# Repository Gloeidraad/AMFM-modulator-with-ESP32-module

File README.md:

This is an MP3 player, Web-radio player, Bluetooth player, and simple waveform generator, based on an ESP32 module. 
The output is connected to a simple FM/AM modulator. The player is intended for collectors and enthusiasts of old
(tube) radios.

The original design (V1.5) has been made with KiCad 7.0. The updated design (V1.7) has been made with KiCad 8.0.

I also added some of the specific 3D models.

Note: In many countries it is not allowed to build radio transmitters. Although this design has a range of only a 
few meters, building it is at your own risk.

Additional information can be found at: 

https://www.transistorforum.nl/forum/index.php?id=77783 and https://www.transistorforum.nl/forum/index.php?id=82213

It is in Dutch, so please use some translate program...

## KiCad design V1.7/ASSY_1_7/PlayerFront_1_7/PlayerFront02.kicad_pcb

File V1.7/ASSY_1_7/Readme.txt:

This section contains designs for a front and back panel for the AM/FM modulator. You find them in the PlayerBack_1_7 and PlayerFront_1_7 directories. You can order the panels at a PCB supplyer or any other panel manufacturer. I recommend a panel thickness of 1 or 1.2 mm. Note that the front panel has also some electronics desing at the back side. This is not used the for player, and can be left wihtout electronic parts.

The main desing (PLL_AM_OSC_1_7_ASSY) is not intended for fabrication, but serves only as a model to show the complete design (case, PCBA, and panels).

Please unzip PLL_AM_OSC_1_7.zip in folder 3D before opening PLL_AM_OSC_1_7_ASSY.kicad_pro

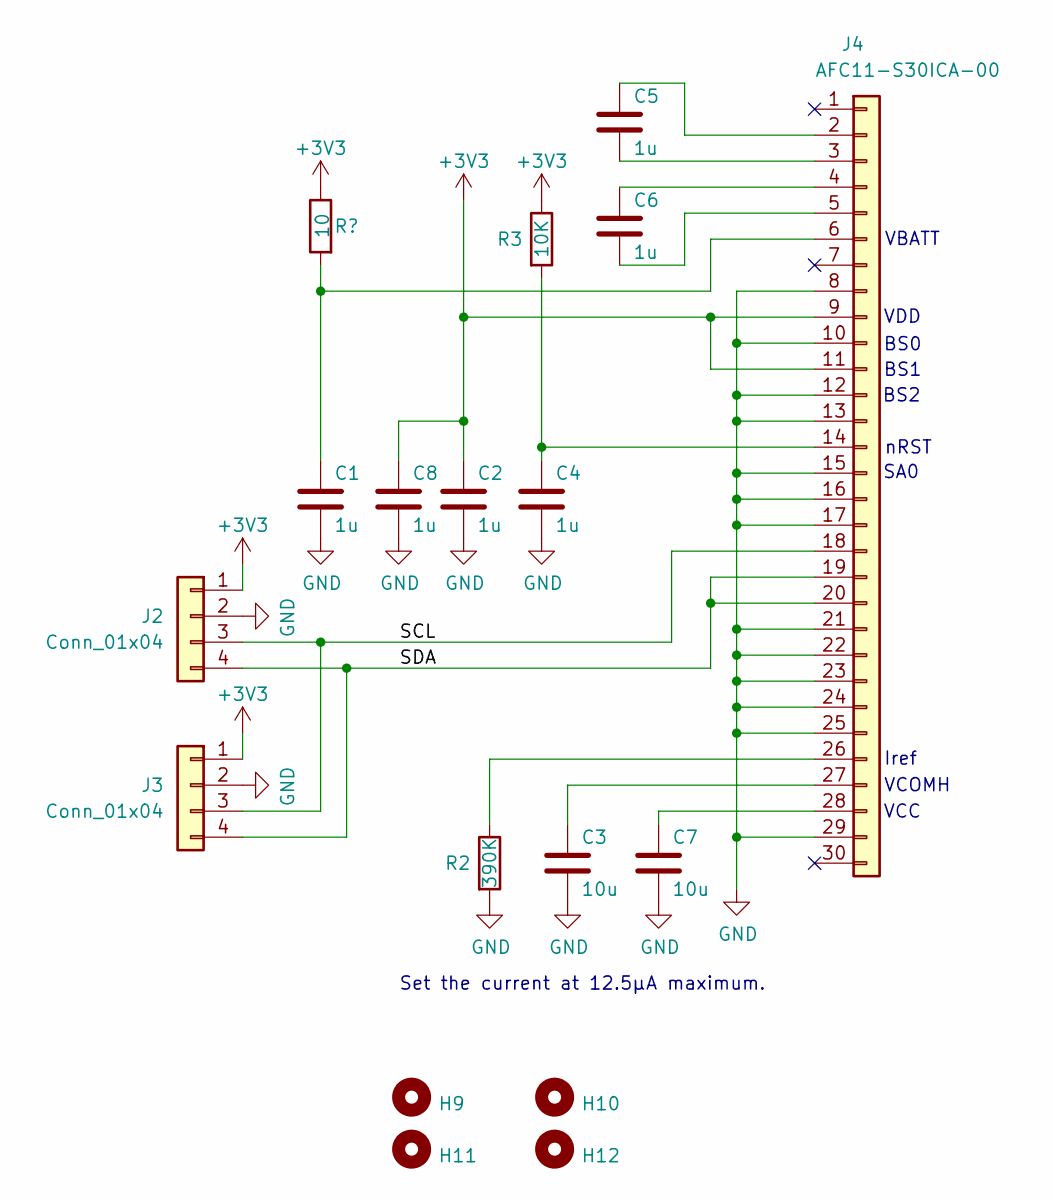
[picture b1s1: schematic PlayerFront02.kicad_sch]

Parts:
C1, C2, C4, C5, C6, C8: 1u; C_1206_3216Metric_Pad1.33x1.80mm_HandSolder
C3, C7: 10u; C_1206_3216Metric_Pad1.33x1.80mm_HandSolder
H9, H10, H11, H12: MountingHole; MountingHole_3.5mm
J2: Conn_01x04; HeaderMale_1x04_P2.54mm_Vertical_SMD
J3: Conn_01x04; PinHeader_1x04_P2.54mm_Vertical_SMD_Pin1Left
J4: AFC11-S30ICA-00; AFC11-S30ICA-00 FFC FPC Connector 0.5mm Pitch 30 pins VERTI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
R2: 390K; R_1206_3216Metric_Pad1.30x1.75mm_HandSolder; JLC C23150
R3: 10K; R_1206_3216Metric_Pad1.30x1.75mm_HandSolder
R10: 10; R_1206_3216Metric_Pad1.30x1.75mm_HandSolder

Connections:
+3V3: C2.1, C8.1, J2.1, J3.1, J4.9, J4.11, R3.1; also elsewhere on the board
/SCL: J2.3, J3.3, J4.18
/SDA: J2.4, J3.4, J4.19, J4.20
GND: C1.2, C2.2, C3.2, C4.2, C7.2, C8.2, J2.2, J3.2, J4.8, J4.10, J4.12, J4.13, J4.15, J4.16, J4.17, J4.21, J4.22, J4.23, J4.24, J4.25, J4.29, R2.2
unnamed: C5.1, J4.2
unnamed: C5.2, J4.3
unnamed: C6.1, J4.4
unnamed: C6.2, J4.5
unnamed 8: C1.1, J4.6; also elsewhere on the board
unnamed: C4.1, J4.14, R3.2
unnamed: J4.26, R2.1
unnamed: C3.1, J4.27
unnamed: C7.1, J4.28

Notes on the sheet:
Set the current at 12.5μA maximum.
VDD
SA0
BS2
BS0
nRST
Iref
VCOMH
VBATT
VCC
BS1

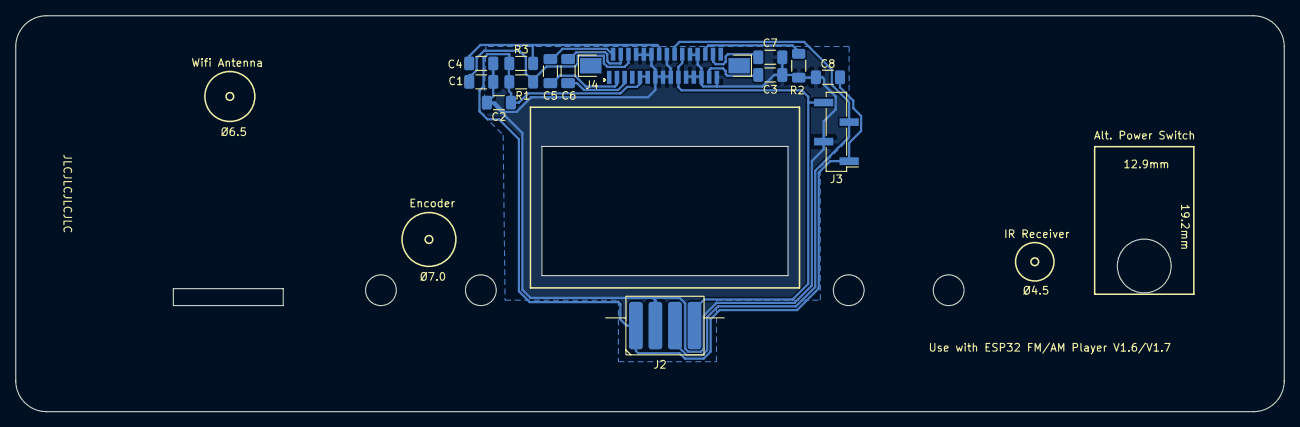
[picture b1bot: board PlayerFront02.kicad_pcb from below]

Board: 2 copper layers, 165.0 x 51.5 mm, 18 parts (14 on the bottom side), 13 nets.

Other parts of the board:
R1: 10; R_1206_3216Metric_Pad1.30x1.75mm_HandSolder

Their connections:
+3V3: R1.1; also elsewhere on the board
unnamed 8: R1.2; also elsewhere on the board

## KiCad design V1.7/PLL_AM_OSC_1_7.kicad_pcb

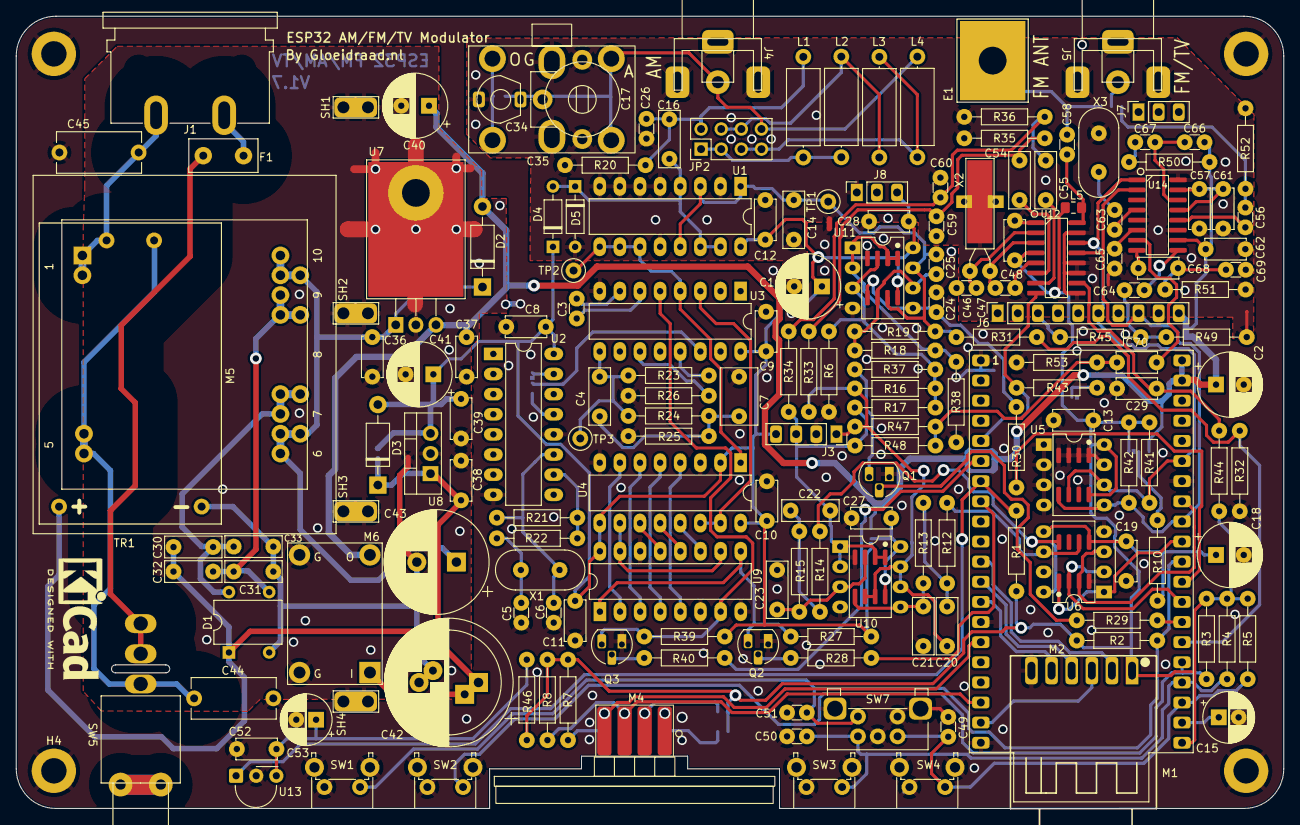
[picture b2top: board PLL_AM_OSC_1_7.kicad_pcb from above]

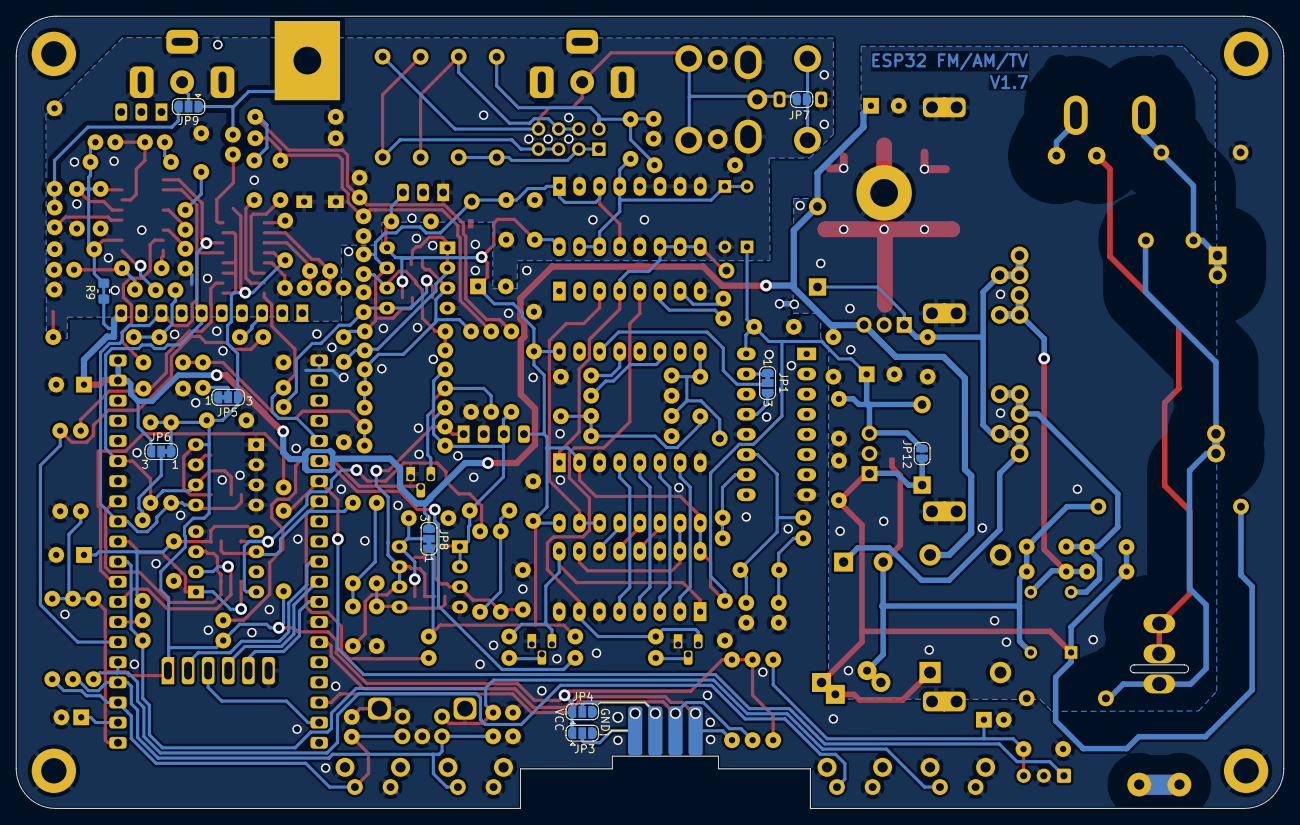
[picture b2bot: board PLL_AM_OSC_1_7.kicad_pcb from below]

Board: 2 copper layers, 160.0 x 100.0 mm, 198 parts (11 on the bottom side), 117 nets.

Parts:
C1, C40, C41: 220µF; CE_Radial_D8.0mm_P3.50mm_E2.0mm
C2: 1000µF; CE_Radial_D8.0mm_P3.50mm_E2.0mm
C3: 100p; C_CER_D30_W16_P25_E20_H08
C4, C54, C55: 100n; C_MKT_L70_W25_P50__E20_H08
C5, C25: 47p; C_CER_D30_W16_P25_E20_H08
C6, C63: 27p; C_CER_D30_W16_P25_E20_H08
C7: 470n; C_MKT_L70_W45_P50__E20_H08
C8, C9, C10, C11, C12, C13, C19, C27, C28, C29, C36, C37, C38, C39, C48, C52, C57, C61: 100n; C_CER_D50_W25_P50_E20_H08
C14: 2n2; C_MKT_L70_W25_P50__E20_H08
C15: 10µF; CE_Radial_D6.3mm_P2.50mm_E2.0mm
C16: 10n; C_MKT_L70_W25_P50__E20_H08
C17: 120p; GZC18100
C18: 100µF; CE_Radial_D8.0mm_P3.50mm_E2.0mm
C20, C22: 1n; C_MKT_L70_W25_P50__E20_H08
C21, C23: 470p; C_MKT_L70_W25_P50__E20_H08
C24, C49, C50, C51, C56, C64: 10n; C_CER_D30_W16_P25_E20_H08
C26, C46, C47: 15p; C_CER_D30_W16_P25_E20_H08
C30, C31, C32, C33: 22n; C_MKT_L70_W25_P50__E20_H08
C34: 120p; TZ03
C35: 142+59 pF; CAP-VAR-223P-NO-CY
C42: 1000µF; CE_Radial_D16.0mm_P7.50_P5.00mm_E2.4mm
C43: 2200µF; CP_Radial_D13.0mm_P5.00mm
C44, C45: 4n7/Y1; C_Disc_D10.5mm_W5.0mm_P10.00mm
C53: 10u; CE_Radial_D6.3mm_P2.50mm_E2.0mm
C58: 4p7; C_CER_D30_W16_P25_E20_H08
C59, C60: 220p; C_CER_D30_W16_P25_E20_H08
C62: 1µF; C_CER_D50_W25_P50_E20_H08
C65: 470p; C_CER_D30_W16_P25_E20_H08
C66, C69: 22n; C_CER_D30_W16_P25_E20_H08
C67: 47n; C_CER_D30_W16_P25_E20_H08
C68, C70: 220n; C_CER_D50_W25_P50_E20_H08
D1: DIL4/1A; Diode_Bridge_DIP-4_W7.62mm_P5.08mm
D2, D3: 1N4001; D_DO-41_SOD81_P10.16mm_Horizontal
D4, D5: BAT85; D_DO-35_SOD27_P7.62mm_Horizontal
E1: ANTENNA; ANTENNA-V3MM5
F1: 100mA; Fuse_Littelfuse_392Series
H1, H2, H3, H4: MountingHole; MountingHole_3.2mm_M3_DIN965_Pad
J1: 230V~; EURO_AC_BX-180_Movable
J3: Conn_01x04; HeaderFemale_1x04_P2.54mm_Vertical
J4, J5: Keystone 900; Keystone RCA
J6: VIDEO-MODULE; HeaderFemale_1x10_P2.54mm_Vertical
J7, J8: Conn_01x03_Socket; HeaderFemale_1x03_P2.54mm_Vertical
JP1, JP5, JP6, JP8: SolderJumper_3_Bridged12; SolderJumper-3_P1.3mm_Bridged12_RoundedPad1.0x1.5mm_NumberL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
JP2: LSEL; PinHeader_2x04_P2.54mm_Vertical
JP3, JP4, JP9: SolderJumper_3_Bridged12; SolderJumper-3_P1.3mm_Open_RoundedPad1.0x1.5mm
JP7: SolderJumper_Mini_2_Open; SolderJumper-2_P1.3mm_Open_RoundedPad1.0x1.5mm
JP12: SolderJumper_2_Open; SolderJumper-2_P1.3mm_Open_RoundedPad1.0x1.5mm
L1, L2: 330 µH; L_Axial_L9.5mm_D4.0mm_P12.70mm_Horizontal
L3: 180 µH; L_Axial_L9.5mm_D4.0mm_P12.70mm_Horizontal
L4: 100 µH; L_Axial_L9.5mm_D4.0mm_P12.70mm_Horizontal
L5: 120nH; L_0805_2012Metric_Pad1.15x1.40mm_HandSolder
M1: ESP32-WROVER-CAM-40P; ESP32-WROVER-DEV_ON_HEADERS_BARE
M2: µSD CARD MODULE; MOD-USD-ADAPTER18X18-type2
M4: OLED-128x64; OLED128X64-1.3inch-P4-Card-Edge-dual
M5: Hi-Link HLK-5M15; HiLink_5Mxx
M6: CN3903 5V/3A Module; MOD-DC-DC-DUAL
MECH1: KiCad Logo; KiCad-Logo2_6mm_SilkScreen
NT1, NT2, NT3: NetTie_2; NetTie-2_SMD_Pad0.7mm
Q1, Q2, Q3: 2N7000; TO-92_HandSolder
R1, R2, R3, R4, R5, R7, R8, R27, R30, R39, R41, R42, R43, R44: 10k; R_Axial_L6.0mm_D2.0mm_P10.16mm_Horizontal
R6: 100k; R_Axial_L6.0mm_D2.0mm_P10.16mm_Horizontal
R9: 1R; R_0805_2012Metric_Pad1.20x1.40mm_HandSolder
R10, R46: 10R; R_Axial_L6.0mm_D2.0mm_P10.16mm_Horizontal
R12, R13, R14, R15, R35, R36: 7k5; R_Axial_L6.0mm_D2.0mm_P10.16mm_Horizontal
R16, R17, R18, R31, R38, R53: 30k; R_Axial_L6.0mm_D2.0mm_P10.16mm_Horizontal
R19: 220K; R_Axial_L6.0mm_D2.0mm_P10.16mm_Horizontal
R20, R21: 1M; R_Axial_L6.0mm_D2.0mm_P10.16mm_Horizontal
R22, R50: 2K2; R_Axial_L6.0mm_D2.0mm_P10.16mm_Horizontal
R23, R52: 100K; R_Axial_L6.0mm_D2.0mm_P10.16mm_Horizontal
R24: 3K3; R_Axial_L6.0mm_D2.0mm_P10.16mm_Horizontal
R25: 2M2; R_Axial_L6.0mm_D2.0mm_P10.16mm_Horizontal
R26: 5K6; R_Axial_L6.0mm_D2.0mm_P10.16mm_Horizontal
R28, R29, R40, R49: 220R; R_Axial_L6.0mm_D2.0mm_P10.16mm_Horizontal
R32: 8k2; R_Axial_L6.0mm_D2.0mm_P10.16mm_Horizontal
R33, R34: 4K7; R_Axial_L6.0mm_D2.0mm_P10.16mm_Horizontal
R37, R51: 15k; R_Axial_L6.0mm_D2.0mm_P10.16mm_Horizontal
R45: 300R; R_Axial_L6.0mm_D2.0mm_P10.16mm_Horizontal
R47, R48: 180K; R_Axial_L6.0mm_D2.0mm_P10.16mm_Horizontal
SH1, SH2, SH3, SH4: Shield; Shielding-pad-2.5x5.0-H1.5-dual
SW1: DOWN; SW_Tactile_SPST_Angled_PTS645Vx83-2LFS
SW2: UP; SW_Tactile_SPST_Angled_PTS645Vx83-2LFS
SW3: PAUSE/OK; SW_Tactile_SPST_Angled_PTS645Vx83-2LFS
SW4: MENU; SW_Tactile_SPST_Angled_PTS645Vx83-2LFS
SW5: SW_SPDT; SWITCH-C&K-7101
SW7: Rotary Encoder; RotaryEncoder_Bourns_Horizontal_PEC12R-2xxxF-Sxxxx
TP1, TP2, TP3: TestPoint; TestPoint_Loop_D1.80mm_Drill1.0mm_Beaded
TR1: Gerth 387.15.2; Transformer-Dual-Footprint-EI38-EI42
U1: CD4053B; DIP-16_W7.62mm_LongPads
U2: CD4060B; DIP-16_W7.62mm_LongPads
U3: CD4046B; DIP-16_W7.62mm_LongPads
U4: CD40103B; DIP-16_W7.62mm_LongPads
U5: 24LC64; DIP-SO-08_W7.62mm
U6: PT8211; DIP-SO-08_W7.62mm_NC7
U7: 7805; TO-220-3_Horizontal_TabDown
U8: 7815; TO-220-3_Vertical
U9: CD4015B; DIP-16_W7.62mm_LongPads
U10, U11: LM358; DIP-SO-08_W7.62mm
U12: KT0803L; SOIC-16_3.9x9.9mm_P1.27mm_alt1
U13: TSOP4538; Vishay_MINIMOLD-3Pin
U14: MC44BS373CA; SOIC-16_3.9x9.9mm_P1.27mm_alt1
X1: 9.216 MHz; Crystal_HC49-U_Vertical
X2: 32.768kHz; Crystal_AT310_D3.0mm_L10.0mm_Horizontal_1EP_style2
X3: 4.0 MHz; Crystal_HC49-U_Vertical

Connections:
/1 - ESP32/ADC: M1.26 (IN35), R31.2, R32.1
/1 - ESP32/AM-DEPTH: M1.27 (IO32), R29.1
/1 - ESP32/AM-MOD: C14.2, C25.2, R19.1, R31.1, TP1.1, U1.1 (Y1), U1.3 (Z1), U1.13 (X1), U11.7
/1 - ESP32/AUD-AM: C25.1, R18.1, R19.2, U11.6 (-)
/1 - ESP32/AUD-L: C20.1, J3.1, R16.2, R33.2, R47.2, U10.6 (-), U10.7
/1 - ESP32/AUD-R: C22.1, J3.3, R17.2, R34.2, R48.2, U10.1, U10.2 (-)
/1 - ESP32/BCK: M1.31 (IO27), U6.1 (BCK)
/1 - ESP32/CLK: M1.12 (SCK/IO18), M2.4 (CLK)
/1 - ESP32/CS: M1.11 (SS0/IO5), M2.2 (CS)
/1 - ESP32/DAC1: M1.29 (IO25/DAC1), R30.2
/1 - ESP32/DOUT: M1.33 (IO12¹), U6.3 (DIN)
/1 - ESP32/EN: C15.1, M1.22 (EN/~RST)
/1 - ESP32/FCEL-DAT: M1.6 (SS1/IO2¹), R40.1
/1 - ESP32/FM-SW: M1.5 (IO15²), R43.2, U12.8 (SW)
/1 - ESP32/FSEL-CLK: M1.8 (IO4), R28.1
/1 - ESP32/IR: M1.7 (IO0²), R1.2, U13.1 (OUT)
/1 - ESP32/LCH: R12.2, U6.6 (LCH)
/1 - ESP32/MISO: M1.13 (MISO/IO19), M2.5 (MISO)
/1 - ESP32/MOSI: M1.19 (MOSI/IO23), M2.3 (MOSI)
/1 - ESP32/RCH: R14.2, U6.8 (RCH)
/1 - ESP32/SCL1: M1.18 (SCL/IO22), M4.3 (SCL), R8.2
/1 - ESP32/SCL2: J6.6, M1.35 (IO13), R41.2, U5.6 (SCL), U12.14 (SCL), U14.1 (SCL)
/1 - ESP32/SDA1: M1.15 (SDA/IO21), M4.4 (SDA), R7.2
/1 - ESP32/SDA2: J6.8, M1.32 (IO14), R42.2, U5.5 (SDA), U12.13 (SDA), U14.2 (SDA)
/1 - ESP32/SW1: C51.1, M1.30 (IO26/DAC2), R2.2, SW1.1, SW7.S1
/1 - ESP32/SW2: M1.25 (IN34), R3.2, SW2.1
/1 - ESP32/SW3: C50.1, M1.24 (IN39/SVN), R4.2, SW3.1, SW7.A
/1 - ESP32/SW4: C49.1, M1.23 (IN36/SVP), R5.2, SW4.1, SW7.B
/1 - ESP32/TV-MONO: C70.1, R47.1, R48.1, R53.2
/1 - ESP32/WS: M1.28 (IO33), U6.2 (WS)
/2 - HF AM_FM/AM-ANT: C17.1, C34.1, C35.1, J4.1 (In), JP2.8, JP7.2, L4.1
/2 - HF AM_FM/DIV-CLK: Q2.3 (D), R27.1, U9.1 (CLKB), U9.9 (CLKA)
/2 - HF AM_FM/DIV-DAT: Q3.3 (D), R39.1, U3.5 (INH), U9.7 (DATA)
/2 - HF AM_FM/F9KHz: JP1.2 (C), U3.14 (SIN)
/2 - HF AM_FM/FM-LEFT: C54.1, C59.1, R33.1, R35.1
/2 - HF AM_FM/FM-RIGHT: C55.1, C60.1, R34.1, R36.1
/2 - HF AM_FM/FMOUT: C58.2, E1.1 (A), JP9.1 (A)
/2 - HF AM_FM/FMOUT2: C58.1, L5.2, U12.16 (OUT)
/2 - HF AM_FM/Ffeed: U3.3 (CIN), U4.14 (~CO/ZD), U4.15 (~SPE)
/2 - HF AM_FM/Fosc: TP2.1, U1.9 (C), U1.10 (B), U1.11 (A), U3.4 (VCO), U4.1 (CLK)
/2 - HF AM_FM/P0: U4.4 (P0), U9.5 (Q1A)
/2 - HF AM_FM/P1: U4.5 (P1), U9.4 (Q2A)
/2 - HF AM_FM/P2: U4.6 (P2), U9.3 (Q3A)
/2 - HF AM_FM/P3: U4.7 (P3), U9.2 (Q4B)
/2 - HF AM_FM/P4: U4.10 (P4), U9.10 (Q4A), U9.15 (DATB)
/2 - HF AM_FM/P5: U4.11 (P5), U9.13 (Q1B)
/2 - HF AM_FM/P6: U4.12 (P6), U9.12 (Q2B)
/2 - HF AM_FM/P7: U4.13 (P7), U9.11 (Q3B)
/2 - HF AM_FM/TVOUT: C56.2, JP9.3 (B), R52.2
/3 - POWER SUPPLY/0V: C31.2, C33.2, C42.2, C43.2, D1.2 (-), M5.3 (-), NT1.1
/3 - POWER SUPPLY/20V: C30.2, C32.2, C38.1, C42.1, D1.1 (+), D3.1 (K), JP12.1 (A), M5.4 (+), M6.1 (VIN+), U8.1 (IN)
/3 - POWER SUPPLY/AC1: C31.1, C32.1, D1.3, TR1.9 (SC)
/3 - POWER SUPPLY/AC2: C30.1, C33.1, D1.4, TR1.7 (SB)
/3 - POWER SUPPLY/ACT: C36.1, C43.1, D2.1 (K), TR1.6 (SA), TR1.10 (SD), U7.1 (IN)
/3 - POWER SUPPLY/L: C45.2, J1.2 (AC_N), M5.2 (AC1), TR1.1 (AA)
/3 - POWER SUPPLY/N1: F1.1, SW5.2 (B), SW5.3 (A)
/3 - POWER SUPPLY/N2: C44.2, M5.1 (AC2), SW5.1 (C), TR1.5 (AB)
GND: C2.2, C5.2, C6.2, C7.1, C8.1, C9.1, C10.1, C11.1, C13.2, C15.2, C18.2, C19.2, C21.2, C23.2, C24.2, C27.2, C28.2, C29.2, C44.1, C45.1, C49.2, C50.2, C51.2, C52.2, C53.2, H1.1, H2.1, H3.1, H4.1, J3.2, J6.9, JP3.3 (B), JP4.3 (B), JP5.1 (A), M1.1 (GND), M1.14 (GND), M1.20 (GND), M1.34 (GND), M2.6 (GND), NT2.1, NT3.1, Q1.1 (S), Q2.1 (S), Q3.1 (S), R6.2, R25.1, R26.1, R32.2, R38.2, R53.1, SW1.2, SW1.H, SW2.2, SW2.H, SW3.2, SW3.H, SW4.2, SW4.H, SW7.C, SW7.MP, SW7.S2, U2.8 (GND), U2.12 (RST), U3.8 (GND), U4.3 (~CI/CE), U4.8 (GND), U5.1 (A0), U5.2 (A1), U5.3 (A2), U5.4 (GND), U5.7 (WP), U6.4 (GND), U9.6 (RSTA), U9.8 (GND), U9.14 (RSTB), U10.4 (V-), U11.4 (V-), U13.2 (GND)
GND1: C36.2, C37.2, C38.2, C39.2, C40.2, C41.2, M6.2 (VIN-), M6.4 (VOUT-), NT1.2, NT2.2, SH1.1, SH2.1, SH3.1, SH4.1, U7.2 (GND), U8.2 (GND)
unnamed: C4.1, C7.2, R24.1, R25.2
unnamed: C5.1, R22.1, X1.1
unnamed: C16.1, C26.1, JP2.2, L1.1, R20.1
unnamed: C20.2, R12.1, R13.2
unnamed: C22.2, R14.1, R15.2
unnamed: C63.2, X3.1
unnamed: C64.1, R45.1, R49.2
unnamed: C67.2, R50.1
unnamed: C68.2, C69.2, R51.1
unnamed: C16.2, D4.2 (A), D5.1 (K), U1.4 (Z), U1.14 (X), U1.15 (Y)
unnamed: F1.2, J1.1 (AC_P)
unnamed: J5.1 (In), JP9.2 (C)
unnamed: J6.3, R45.2
unnamed: JP1.1 (A), U2.15 (Q10)
unnamed: JP1.3 (B), U2.13 (Q9)
unnamed: JP2.1, JP2.3, L1.2, L2.2
unnamed: JP2.4, JP2.6, L2.1, L3.2
unnamed: JP2.5, JP2.7, L3.1, L4.2
unnamed: JP3.2 (C), M4.1 (GND)
unnamed: JP4.2 (C), M4.2 (VCC)
unnamed: JP5.2 (C), R43.1
unnamed: JP6.2 (C), R10.1
unnamed: C35.3, JP7.1 (A)
unnamed: C27.1, JP8.2 (C), U10.8 (V+)
unnamed: Q1.3 (D), R37.1
unnamed: Q1.2 (G), R29.2
unnamed: Q2.2 (G), R28.2
unnamed: Q3.2 (G), R40.2
unnamed: C6.1, R21.1, U2.11 (RS), X1.2
unnamed: R21.2, R22.2, U2.10 (RTC)
unnamed: C3.2, U3.6 (C1A)
unnamed: C3.1, U3.7 (C1B)
unnamed: R23.2, U3.13 (P2)
unnamed: R26.2, U3.11 (R1)
unnamed: C4.2, R23.1, R24.2, TP3.1, U3.9 (VCIN)
unnamed: C23.1, R15.1, U10.3 (+)
unnamed: C21.1, R13.1, U10.5 (+)
unnamed: R6.1, R16.1, R17.1, R37.2, U11.3 (+)
unnamed: R18.2, R38.1, U11.1, U11.2 (-)
unnamed: C24.1, R30.1, U11.5 (+)
unnamed: C54.2, U12.6 (INL)
unnamed: C55.2, U12.7 (INR)
unnamed: C46.1, U12.2 (XI), X2.2
unnamed: C47.1, U12.3 (XO), X2.1
unnamed: C29.1, R44.2, U12.10 (~RST)
unnamed: C52.1, C53.1, R46.2, U13.3 (Vs)
unnamed: C70.2, U14.7 (AUDIO)
unnamed: C66.1, C67.1, U14.14 (PLLFLT)
unnamed: C65.1, U14.6 (PREEM)
unnamed: C68.1, U14.8 (SPLLFLT)
unnamed: C56.1, U14.12 (TVOUT)
unnamed: C64.2, U14.9 (VIDEO)
unnamed: C63.1, U14.4 (XTAL)
RFGND: C1.2, C12.1, C14.1, C17.2, C26.2, C34.2, C35.2, C46.2, C47.2, C48.1, C57.2, C59.2, C60.2, C61.2, C62.2, C65.2, C69.1, D5.2 (A), J4.2 (Ext), J5.2 (Ext), J8.1, NT3.2, R20.2, R35.2, R36.2, R49.1, R51.2, R52.1, U1.2 (Y0), U1.5 (Z0), U1.6 (~EN), U1.7 (VEE), U1.8 (GND), U1.12 (X0), U12.1 (GND), U12.5 (GND), U12.9 (GND), U12.11 (GND), U12.12 (GND), U12.15 (GND), U14.5 (GND), U14.11 (GND), U14.16 (GNDD), X2.3, X3.2
V3.3: C13.1, C48.2, JP3.1 (A), JP4.1 (A), JP5.3 (B), JP6.1 (A), L5.1, M1.21 (3V3), M2.1 (VDD), R1.1, R2.1, R3.1, R4.1, R5.1, R7.1, R8.1, R41.1, R42.1, R44.1, R46.1, U5.8 (VCC), U12.4 (VDD)
V5: C2.1, C37.1, C40.1, C57.1, C61.1, C62.1, C66.2, D2.2 (A), J6.10, JP6.3 (B), JP8.3 (B), M1.39 (5V), M1.40 (5V), M6.3 (VOUT+), R9.1, R9.2, R50.2, U7.3 (OUT), U14.10 (VCCA), U14.13 (TVOVCC), U14.15 (VCCD)
V15: C1.1, C8.2, C9.2, C10.2, C11.2, C12.2, C28.1, C39.1, C41.1, D3.2 (A), D4.1 (K), J3.4, J8.3, JP8.1 (A), JP12.2 (B), R27.2, R39.2, U1.16 (VCC), U2.16 (VCC), U3.16 (VDD), U4.2 (~CLR), U4.9 (~APE), U4.16 (VDD), U8.3 (OUT), U9.16 (VDD), U11.8 (V+)
VDDdac: C18.1, C19.1, R10.2, U6.5 (VDD)

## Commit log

2024-01-03 Create production
    Gerbers
2024-01-03 readme.txt
2024-01-06 Create build instructions
2024-01-07 Update build instructions
2024-01-07 Typo
2024-06-23 Add files via upload
    Moved from src root
2024-06-23 Add files via upload
    Include libraries in project
2024-06-23 Add files via upload
    Include libraries in project
2024-06-23 Delete software/ESP32-AM-FM-Modulator/src/Board.h
    Moved to directory "Hardware"
2024-06-23 Delete software/ESP32-AM-FM-Modulator/src/CD4015B.cpp
    Moved to directory "Hardware"
2024-06-23 Delete software/ESP32-AM-FM-Modulator/src/CD4015B.h
    Moved to directory "Hardware"
2024-06-23 Delete software/ESP32-AM-FM-Modulator/src/KT0803X.cpp
    Moved to directory "Hardware"
2024-06-23 Delete software/ESP32-AM-FM-Modulator/src/KT0803X.h
    Moved to directory "Hardware"
2024-06-23 Delete software/ESP32-AM-FM-Modulator/src/NFOR_SSD1306.cpp
    Moved to directory "Hardware"
2024-06-23 Delete software/ESP32-AM-FM-Modulator/src/NFOR_SSD1306.h
    Moved to directory "Hardware"
2024-06-23 Delete software/ESP32-AM-FM-Modulator/src/NFOR_SSD1306_fonts.cpp
    Moved to directory "Hardware"
2024-06-23 Delete software/ESP32-AM-FM-Modulator/src/NFOR_SSD1306_fonts.h
    Moved to directory "Hardware"
2024-06-23 Delete software/ESP32-AM-FM-Modulator/src/PT8211.cpp
    Moved to directory "Hardware"
2024-06-23 Delete software/ESP32-AM-FM-Modulator/src/PT8211.h
    Moved to directory "Hardware"
2024-06-23 Update build instructions
    Project now includes the used libraries.
2024-06-25 Update build instructions
    Added instructions about board package
2024-07-06 Prepared for compilation with Arduino ESP32 3.0.x
2024-07-06 Rename build instructions to build instructions.txt
2024-07-20 Rename PLL_AM_OSC_1_5a.kicad_pcb to V1.5/PLL_AM_OSC_1_5a.kicad_pcb
2024-07-20 Rename PLL_AM_OSC_1_5a.kicad_pro to V1.5/PLL_AM_OSC_1_5a.kicad_pro
2024-07-20 Rename production/PLL_AM_OSC_1_5a.pdf to V1.5/production/PLL_AM_OSC_1_5a.pdf
2024-07-20 Rename production/PLL_AM_OSC_1_5a.xlsx to V1.5/production/PLL_AM_OSC_1_5a.xlsx
2024-07-20 Rename production/PLL_AM_OSC_1_5a.zip to V1.5/production/PLL_AM_OSC_1_5a.zip
2024-07-20 Rename images/PCB.png to V1.5/images/PCB.png
2024-07-20 Rename images/Foto met 2x7V5.jpg to V1.5/images/Foto met 2x7V5.jpg
2024-07-20 Rename images/elechouse.jpg to V1.5/images/elechouse.jpg
2024-07-21 Add files via upload
    Something went wrong moving the files to V1.5. Uploaded again.
2024-07-24 Added URL about V1.7
2024-07-28 Add files via upload
    This is the (unverified) design of the front panel for the V1.5 PCBA. For using this design,
    you have to install the 1.3 inch OLED display on the PCBA. if you want to use the 0.96 inch
    OLED display, you have to modify the viewing opening.
2024-08-04 Adjusted mounting holes
    Made mounting holes a bit oval, to enable tiny positional adjustments.
2024-08-28 Fixed initialisation error in SimpleWaveGenerator
2024-10-04 Improved track and url selection
    Tracks and URLs can now be selected by name, rather than by number
2025-02-01 Removed dangling #endif
